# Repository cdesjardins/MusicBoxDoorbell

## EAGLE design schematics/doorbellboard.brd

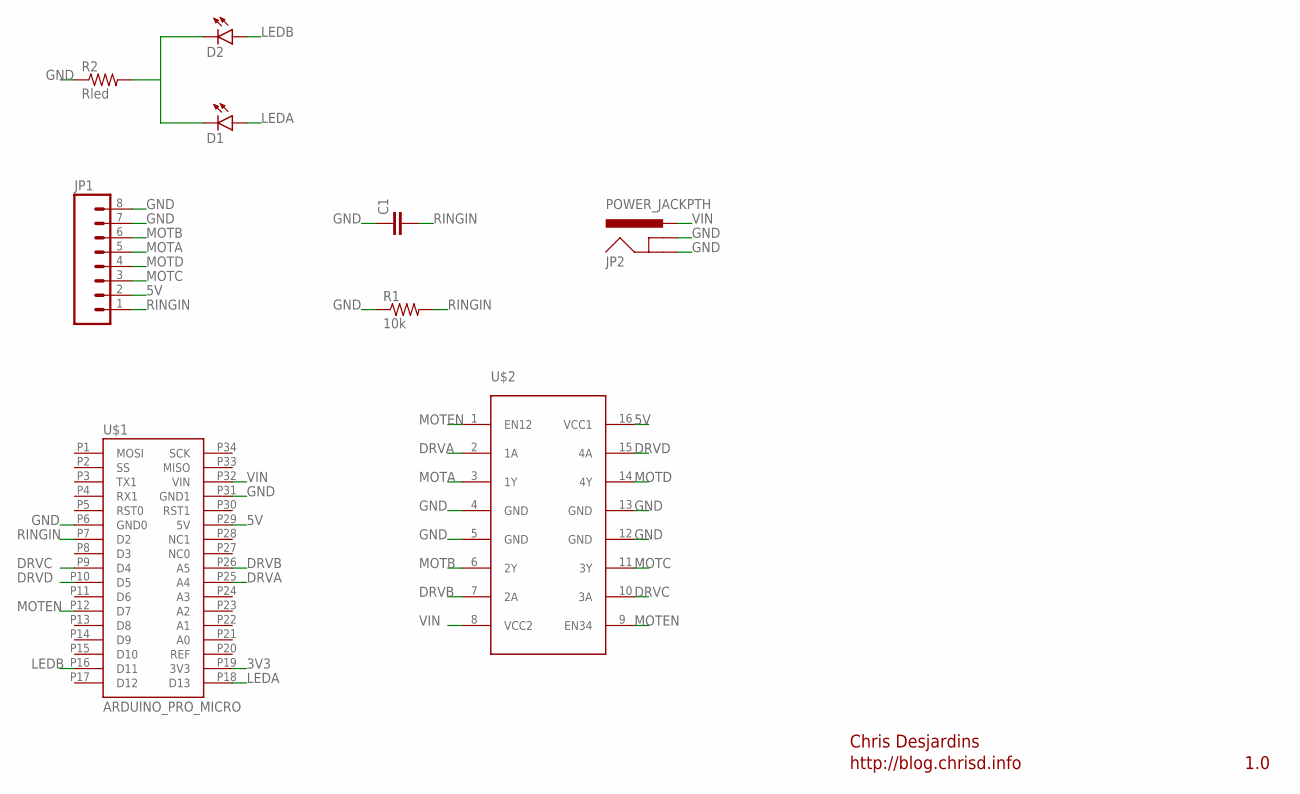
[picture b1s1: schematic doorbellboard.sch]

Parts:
C1: 0.1UF-50V-20%(PTH)KIT-EZ; CAP-PTH-SMALL-KIT
D1, D2: LED-3MM-NO_SILK; LED3MM-NS
JP1: M08; 1X08_ROUND
JP2: POWER_JACKPTH; POWER_JACK_PTH
R1: 10k; AXIAL-0.3
R2: Rled; AXIAL-0.3
U$1: ARDUINO_PRO_MICRO
U$2: SN754410; DIL16-KIT

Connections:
3V3: U$1.P19 (3V3)
5V: JP1.2, U$1.P29 (5V), U$2.16 (VCC1)
DRVA: U$1.P25 (A4), U$2.2 (1A)
DRVB: U$1.P26 (A5), U$2.7 (2A)
DRVC: U$1.P9 (D4), U$2.10 (3A)
DRVD: U$1.P10 (D5), U$2.15 (4A)
GND: C1.1, JP1.7, JP1.8, JP2.GND, JP2.GNDBREAK, R1.P$1 (1), R2.P$1 (1), U$1.P6 (GND0), U$1.P31 (GND1), U$2.4 (GND), U$2.5 (GND), U$2.12 (GND), U$2.13 (GND)
LEDA: D1.A, U$1.P18 (D13)
LEDB: D2.A, U$1.P16 (D11)
LEDOUT: D1.K (C), D2.K (C), R2.P$2 (2)
MOTA: JP1.5, U$2.3 (1Y)
MOTB: JP1.6, U$2.6 (2Y)
MOTC: JP1.3, U$2.11 (3Y)
MOTD: JP1.4, U$2.14 (4Y)
MOTEN: U$1.P12 (D7), U$2.1 (EN12), U$2.9 (EN34)
REF: U$1.P20 (REF)
RINGIN: C1.2, JP1.1, R1.P$2 (2), U$1.P7 (D2)
VIN: JP2.PWR, U$1.P32 (VIN), U$2.8 (VCC2)

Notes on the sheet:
Chris Desjardins
1.0
http://blog.chrisd.info

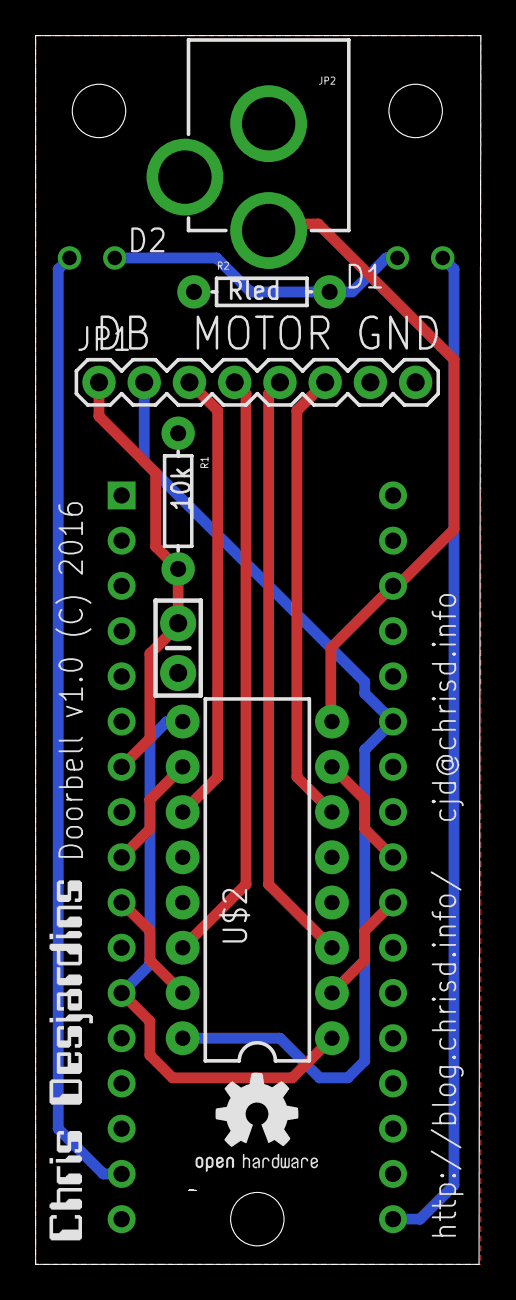
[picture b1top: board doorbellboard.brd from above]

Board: 2 copper layers, 25.0 x 69.0 mm, 11 parts (0 on the bottom side), 16 nets.

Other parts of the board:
U$3: LOGO
U$4: OSHW2

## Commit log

2016-01-12 Adding first drawings
2016-01-16 Adding motor mount outline
2016-01-16 add motor mount
2016-01-16 Line up motor mount and music box
2016-01-17 Add arduino code for the doorbell
2016-01-17 Remove some debug code
2016-01-17 Made the logic a bit more logical
2016-01-17 Get rid of dead code
2016-01-18 Add debug to make sure there are no phantom rings
2016-01-18 Untabify
2016-01-19 Add copyright
2016-01-27 Up the revs per ring
2016-01-27 Add schematics for doorbell board
2016-01-27 Add OSHW logo
2016-01-27 Add name/website/version
2016-02-02 Final setup for acutal doorbell
2016-02-02 Update plastics for stepper
2016-02-06 Add image of the doorbell board
2016-02-06 Add readme
2016-02-06 Rotate board
2016-02-07 Disable interrupts during process
2016-02-10 Add some LEDs
2016-02-13 Update png to latest
2016-03-12 Fixup pins for V1.0
2016-07-30 Remove unused code, and put debug on serial1
2016-07-31 Cleanup code, and add sleep mode
2018-02-26 Drive all stepper pins low on disable
2018-02-26 Get rid of ring count
2018-02-26 Add sleeping state
    Previously the arduiono was going to sleep, but the
    stepper was still drawing current because it was
    not being disabled properly, the new sleeping state
    fixes this.

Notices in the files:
schematics/doorbellboard.brd:
Doorbell v1.0 (C) 2016
parts and their libraries:
SparkFun-Connectors: Licensing: Creative Commons ShareAlike 4.0 International - https://creativecommons.org/licenses/by-sa/4.0
